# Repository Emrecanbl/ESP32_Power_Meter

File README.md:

# ESP32-S3 Power Meter (INA3221 ·  TFT · Qt Ui · SQLlite data base)

An ESP32-S3–based **three-channel power meter** built around INA3221. One channel supports **USB-C pass-through** so you can measure power flowing from **USB-C IN → USB-C OUT**; **CC pins are tied** for basic PD trigger behavior (power-only path).

> Firmware stack: **FreeRTOS**.
> REST/WebSocket API is **optional** (may be added later).
> Live data can be streamed over **USB-CDC**; an **optional ST7735 (160×128) SPI TFT** can show basic status (no touch).
>
> A custom **3D-printed enclosure** is planned.

---

---

## Features

* **3 measurement channels** via **INA3221**

  * Voltage (V), Current (A), Power (W), accumulated **mAh / mWh**
* **ESP32-S3** (Wi‑Fi + native USB/CDC)

  * UART header and USB device available on the board
* **USB‑C pass‑through (1 channel)**: measure power across IN → OUT

  * **CC lines tied** (basic PD role trigger; data lines not routed)
* **Optional TFT:** **ST7735 (160×128) SPI** for basic on-device status (no touch)
* **Battery**: **TP4056** Li‑ion charger + **AMS1117‑3.3** LDO
* **Enclosure**: custom **3D‑printed** case (to be published)

---

## What’s New

* Qt UI with Python and SQLite database integration

* Added boot-time Check screen: verifies Wi‑Fi link and sensor health before entering the UI.

* Check screen now shows connection status and the assigned IP address.

* Main screen updated to display the device IP for quick access to the Web UI.

* **ST7735 (160×128) screen added (no touch).**

* Energy counter buttons are active (Start/Stop/Reset)

* Sensor → UART JSON and Web UI hooked up

* 4-task FreeRTOS skeleton: sensor, screen, web, uart

## Gallery

<p align="center">
  &nbsp;&nbsp;
  <br>
  <em> First Check Screen &nbsp; | &nbsp; Main Screen </em>
</p>

<p align="center">
  &nbsp;&nbsp;
  <br>
  <em> First Run Without Screen &nbsp; | &nbsp; With ST7735</em>
</p>

<p align="center">
  &nbsp;&nbsp;
  <br>
  <em>3D board render &nbsp; | &nbsp; PCB layout</em>
</p>

<p align="center">
  <!-- Add your prototype photos below when ready -->
  &nbsp;&nbsp;
  <em>Prototype (front) </em>
</p>

<p align="center">
  <br>
  <em>Producted PCB (first article)</em>
</p>

<p align="center">
  <br>
  <em>Assembled PCB </em>
</p>

<p align="center">
  <br>
  <em>Schematic (block view)</em>
</p>

<p align="center">
  <br>
  <em> Qt Ui </em>
</p>

## Hardware Overview

* **MCU:** ESP32‑S3 module
* **Power Monitor:** INA3221 (three shunts)
* **Optional Display:** ST7735 (160×128) over SPI (no touch)
* **Power Path:** USB‑C IN, USB‑C OUT (pass‑through on Channel 1)
* **PMICs:** TP4056 Li‑ion charger, AMS1117‑3.3 regulator
* **Connectors:** 3× screw terminals (IN/OUT/GND), UART header, 2× USB‑C

### Block Diagram

```
USB-C IN ──┐                  ┌── USB-C OUT (pass-through)
           ├─ Shunt CH1  ─────┤
IN/OUT CH2 ├─ Shunt CH2  ─────┤──> Loads
IN/OUT CH3 ├─ Shunt CH3  ─────┘
           │
        INA3221  ── I2C ── ESP32-S3 ── SPI ── ST7735 TFT (optional)
                               ├─ (Optional) Wi‑Fi HTTP/WS
                               └─ USB‑CDC / UART (streaming)
```

---

## Default Pins

| Function                       | ESP32‑S3 Pin      |
| ------------------------------ | ----------------- |
| I2C SDA / SCL (INA3221)        | GPIO __ / __      |
| TFT (ST7735) MOSI / MISO / SCK | GPIO __ / __ / __ |
| TFT CS / DC / RST              | GPIO __ / __ / __ |
| UART RX / TX                   | GPIO __ / __      |
| USB‑CDC                        | Native (S3)       |

---

## Firmware (planned)

* **Framework:** FreeRTOS
* **Modules:**

  * `sensor` – INA3221 sampling, filtering, mAh/mWh accumulation
  * `ui` *(optional)* – minimal status pages on **ST7735**; device can run headless
  * *(Optional)* `web` – HTTP + WebSocket for live JSON
  * `usb_stream` – ASCII/JSON streaming over USB‑CDC (no file logging)
* **Example JSON (USB/Web, if enabled):**

```json
{"ch":1,"voltage":5.08,"current":1.12,"power":5.69,"mah_total":23.4,"mwh_total":118.9,"ts":1730529652}
```

---

### Efficiency Measurement

The board can measure real conversion efficiency by comparing input and output power:

* Channels: CH1 = input (P_in), CH2 = output (P_out)
* Instantaneous: η_inst = P_out / P_in
* Averaged (stable): EMA over 1–3 s → η_avg =  P̄_out / P̄_in
* Energy-based: η_energy = ΔmWh_out / ΔmWh_in (robust against short spikes)

## Repo Layout (suggested)

```
/hardware
  schematic.pdf
  gerber/
/firmware
  /main
    board.h
    app_sensor.c
    app_ui_tft.c
    app_usb_stream.c
    (optional) app_web.c
  sdkconfig.defaults
/Photos
  PCB.jpg
  PCB_Model.jpg
  Prototype.jpg
  Prototype_Back1.jpg
  Prototype_Back2.jpg
  Real_PCB.jpg
  Schematic.png
/enclosure
  stl/  (3D-printed case files)
```

---

## Roadmap

* [ ] Bring‑up: INA3221 I2C readout
* [ ] Publish 3D‑printed enclosure (STL)
* [ ] USB‑CDC live streaming (no on‑device logs)
* [ ] Minimal on-device status (ST7735)
* [ ] Calibration UI + NVS storage
* [ ] (Optional) REST/WS endpoints

---

## Notes & Safety

* USB‑C pass‑through is **power‑only** (data lines not connected).
* CC lines support **basic PD trigger behavior**; PD profile support is **limited**.
* Verify shunt resistor wattage and temperature rise.
* Provide adequate thermal copper for **TP4056** during charging.

---

## License

MIT (to be added).

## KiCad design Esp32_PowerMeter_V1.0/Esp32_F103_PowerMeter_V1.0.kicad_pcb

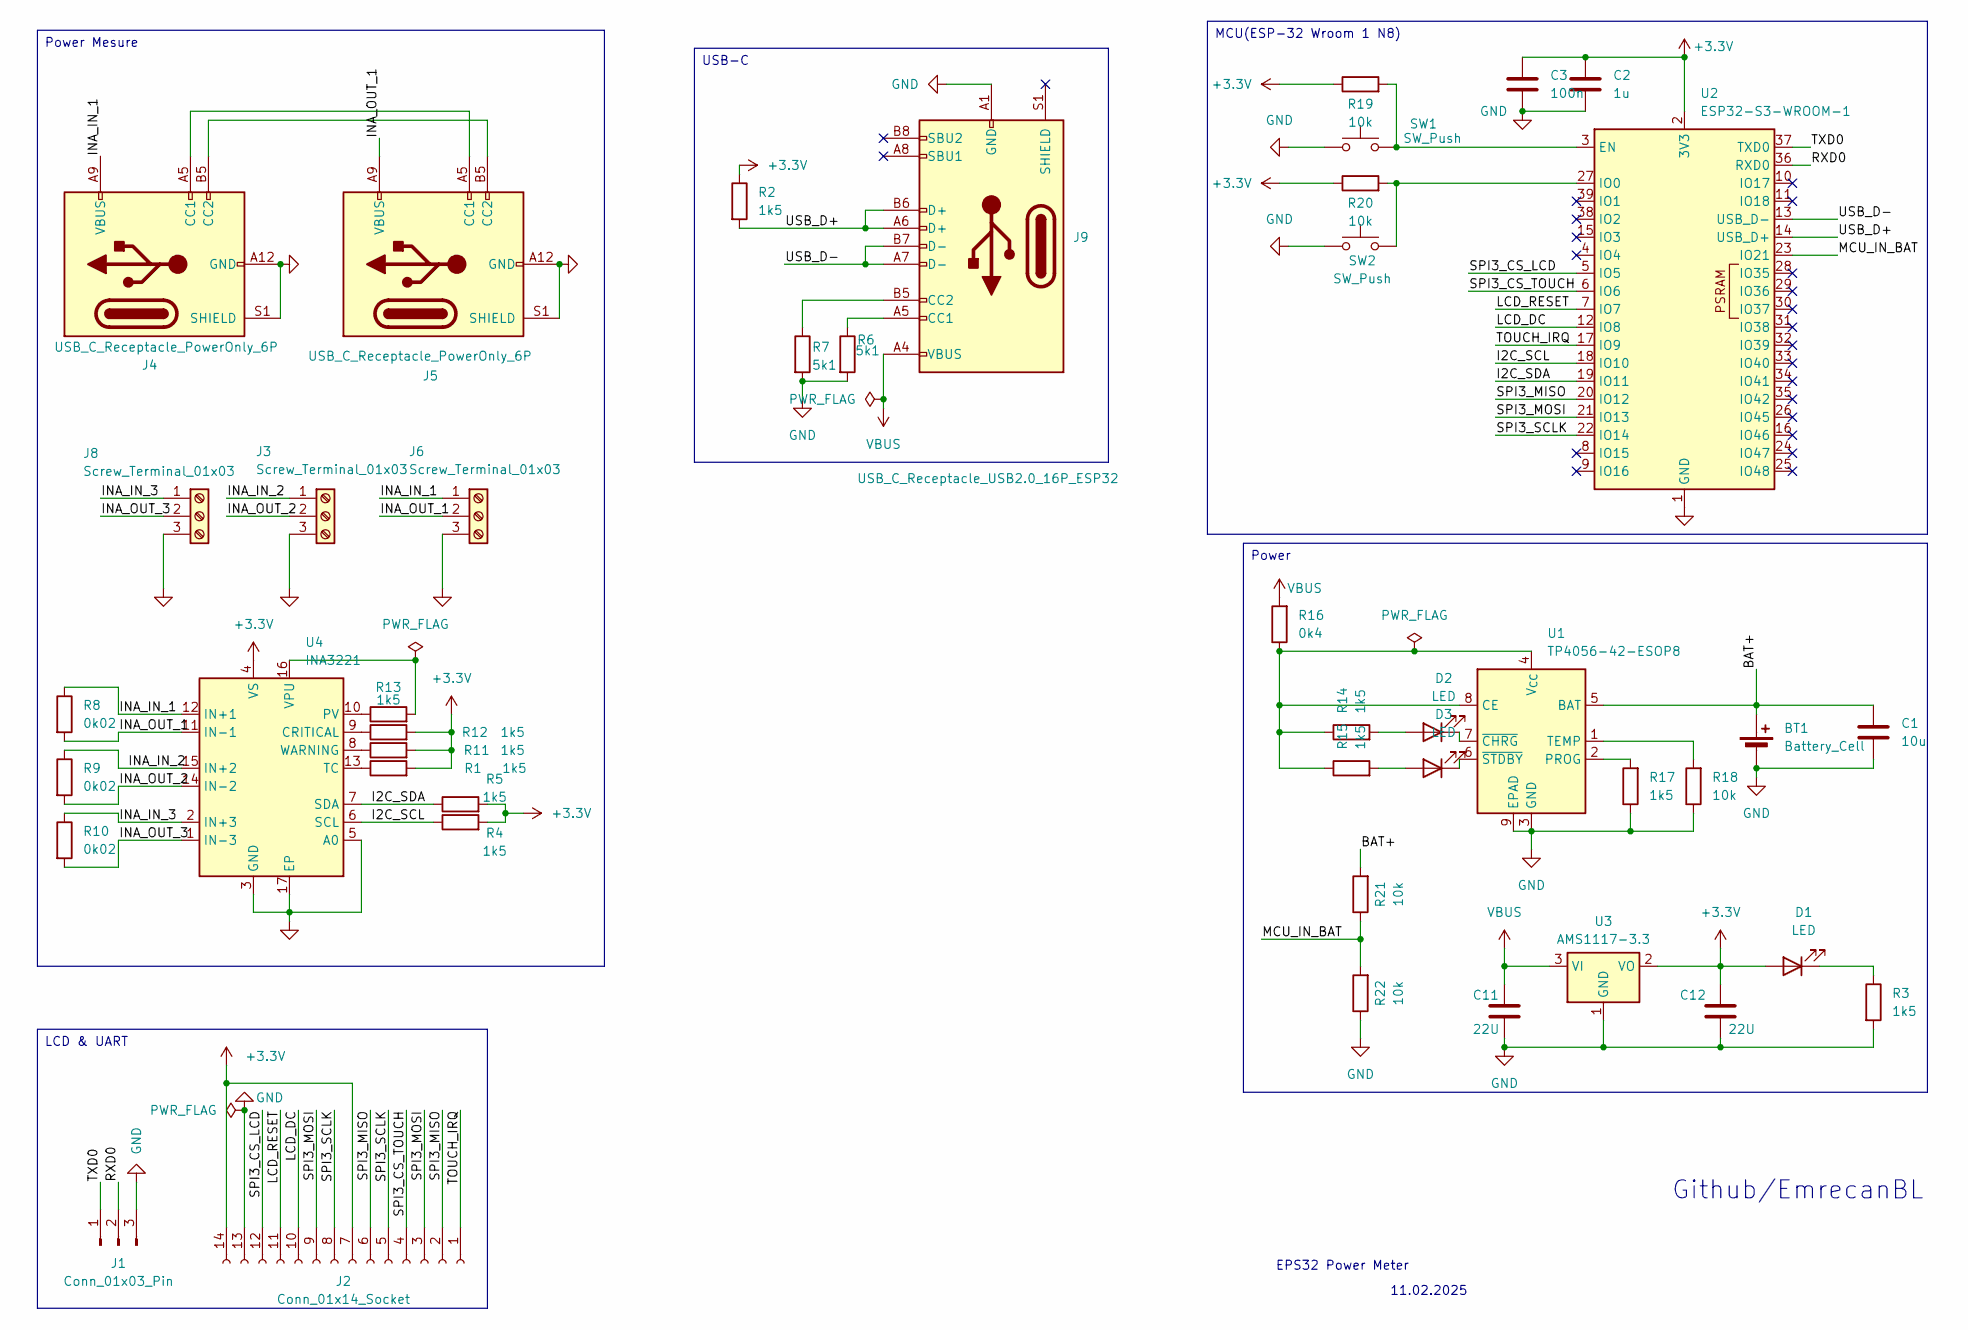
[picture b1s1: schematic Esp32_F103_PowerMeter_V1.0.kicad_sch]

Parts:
BT1: Battery_Cell; Molex_Micro-Fit_3.0_43045-0212_2x01_P3.00mm_Vertical
C1: 10u; C_0402_1005Metric
C2: 1u; C_0402_1005Metric
C3: 100n; C_0402_1005Metric
C11, C12: 22U; C_0603_1608Metric
D1, D2, D3: LED; LED_0603_1608Metric
J1: Conn_01x03_Pin; PinHeader_1x03_P2.54mm_Vertical
J2: Conn_01x14_Socket; PinSocket_1x14_P2.54mm_Vertical
J3, J6, J8: Screw_Terminal_01x03; TerminalBlock_4Ucon_1x03_P3.50mm_Vertical
J4, J5: USB_C_Receptacle_PowerOnly_6P; USB_C_Receptacle_GCT_USB4125-xx-x_6P_TopMnt_Horizontal
J9: USB_C_Receptacle_USB2.0_16P_ESP32; USB_C_Receptacle_GCT_USB4105-xx-A_16P_TopMnt_Horizontal
R1, R2, R3, R4, R5, R11, R12, R13, R14, R15, R17: 1k5; R_0603_1608Metric
R6, R7: 5k1; R_0603_1608Metric
R8, R9, R10: 0k02; R_0603_1608Metric
R16: 0k4; R_0603_1608Metric
R18, R19, R20, R21, R22: 10k; R_0603_1608Metric
SW1, SW2: SW_Push; SW_PUSH_6mm_H4.3mm
U1: TP4056-42-ESOP8; SOIC-8-1EP_3.9x4.9mm_P1.27mm_EP2.41x3.3mm_ThermalVias
U2: ESP32-S3-WROOM-1
U3: AMS1117-3.3; SOT-223-3_TabPin2
U4: INA3221; Texas_RGV0016A_VQFN-16-1EP_4x4mm_P0.65mm_EP2.1x2.1mm

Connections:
+3.3V: C2.1, C3.1, C12.1, D1.2 (A), J2.7, J2.14, R1.2, R2.1, R4.2, R5.2, R11.2, R12.2, R19.1, R20.1, U2.2 (3V3), U3.2 (VO), U4.4 (VS); also elsewhere on the board
/BAT+: BT1.1 (+), C1.1, R21.2, U1.5 (BAT)
/I2C_SCL: R4.1, U2.18 (IO10), U4.6 (SCL)
/I2C_SDA: R5.1, U2.19 (IO11), U4.7 (SDA)
/INA_IN_1: J4.A9 (VBUS), J4.B9 (VBUS), J6.1, R8.1, U4.12 (IN+1)
/INA_IN_2: J3.1, R9.1, U4.15 (IN+2)
/INA_IN_3: J8.1, R10.1, U4.2 (IN+3)
/INA_OUT_1: J5.A9 (VBUS), J5.B9 (VBUS), J6.2, R8.2, U4.11 (IN-1)
/INA_OUT_2: J3.2, R9.2, U4.14 (IN-2)
/INA_OUT_3: J8.2, R10.2, U4.1 (IN-3)
/LCD_DC: J2.10, U2.12 (IO8)
/LCD_RESET: J2.11, U2.7 (IO7)
/MCU_IN_BAT: R21.1, R22.2, U2.23 (IO21)
/RXD0: J1.2, U2.36 (RXD0)
/SPI3_CS_LCD: J2.12, U2.5 (IO5)
/SPI3_CS_TOUCH: J2.4, U2.6 (IO6)
/SPI3_MISO: J2.2, J2.6, U2.20 (IO12)
/SPI3_MOSI: J2.3, J2.9, U2.21 (IO13)
/SPI3_SCLK: J2.5, J2.8, U2.22 (IO14)
/TOUCH_IRQ: J2.1, U2.17 (IO9)
/TXD0: J1.1, U2.37 (TXD0)
/USB_D+: J9.A6 (D+), J9.B6 (D+), R2.2, U2.14 (USB_D+)
/USB_D-: J9.A7 (D-), J9.B7 (D-), U2.13 (USB_D-)
GND: BT1.2 (-), C1.2, C2.2, C3.2, C11.2, C12.2, J1.3, J2.13, J3.3, J4.A12 (GND), J4.B12 (GND), J4.S1 (SHIELD), J5.A12 (GND), J5.B12 (GND), J5.S1 (SHIELD), J6.3, J8.3, J9.A1 (GND), J9.A12 (GND), J9.B1 (GND), J9.B12 (GND), R3.2, R6.2, R7.2, R17.1, R18.1, R22.1, SW1.1, SW2.1, U1.3 (GND), U1.9 (EPAD), U2.1 (GND), U2.40 (GND), U2.41 (GND), U3.1 (GND), U4.3 (GND), U4.5 (A0), U4.17 (EP); also elsewhere on the board
unnamed: D1.1 (K), R3.1
unnamed: D2.2 (A), R14.2
unnamed: D2.1 (K), U1.7 (~CHRG)
unnamed: D3.2 (A), R15.2
unnamed: D3.1 (K), U1.6 (~STDBY)
unnamed: J4.A5 (CC1), J5.A5 (CC1)
unnamed: J4.B5 (CC2), J5.B5 (CC2)
unnamed: J9.A5 (CC1), R6.1
unnamed: J9.B5 (CC2), R7.1
unnamed: R14.1, R15.1, R16.1, U1.4 (V_{CC}), U1.8 (CE)
unnamed: R17.2, U1.2 (PROG)
unnamed: R18.2, U1.1 (TEMP)
unnamed: R19.2, SW1.2, U2.3 (EN)
unnamed: R20.2, SW2.2, U2.27 (IO0)
unnamed: R12.1, U4.9 (CRITICAL)
unnamed: R13.1, U4.10 (PV)
unnamed: R1.1, U4.13 (TC)
unnamed: R13.2, U4.16 (VPU)
unnamed: R11.1, U4.8 (WARNING)
VBUS: C11.1, J9.A4 (VBUS), J9.A9 (VBUS), J9.B4 (VBUS), J9.B9 (VBUS), R16.2, U3.3 (VI)

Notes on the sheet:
11.02.2025
Github/EmrecanBL
EPS32 Power Meter
USB-C
LCD & UART
Power
MCU(ESP-32 Wroom 1 N8)
Power Mesure

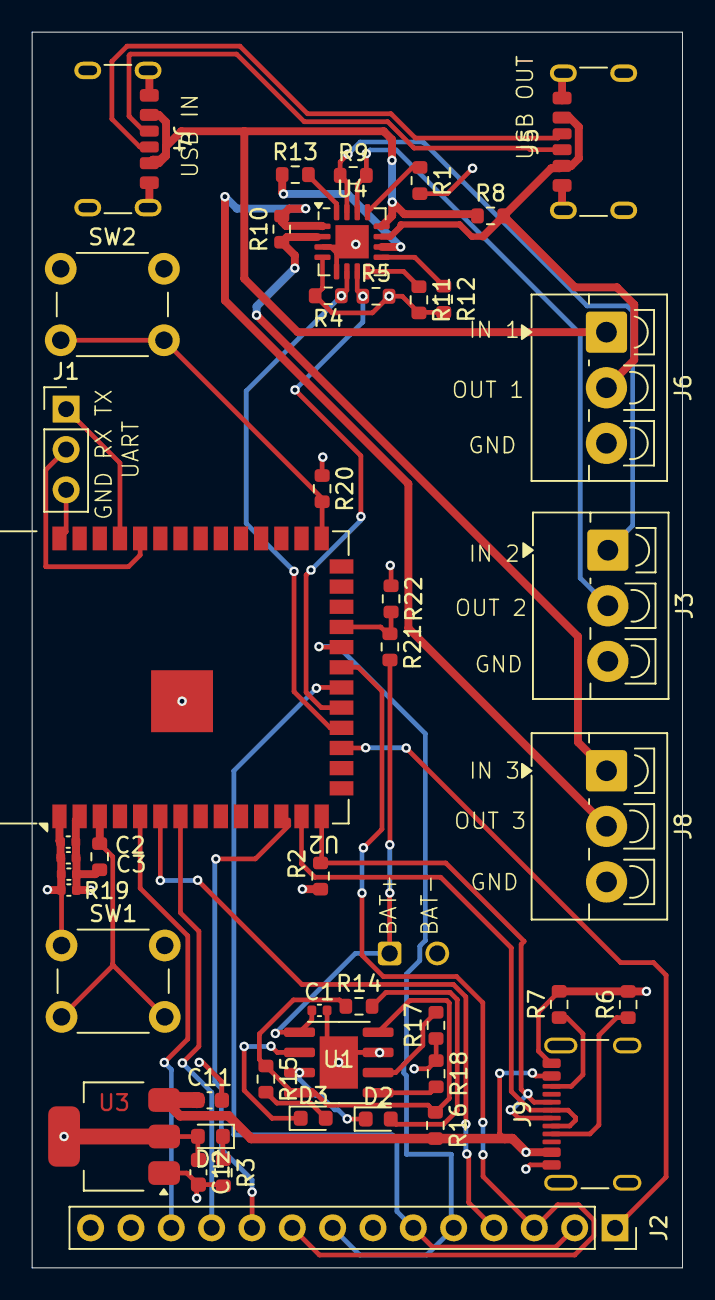
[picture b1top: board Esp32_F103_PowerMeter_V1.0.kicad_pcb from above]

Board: 4 copper layers, 41.0 x 77.8 mm, 47 parts (0 on the bottom side), 44 nets.

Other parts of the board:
C2#2: 1u; C_0402_1005Metric
C3#2: 100n; C_0402_1005Metric

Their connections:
+3.3V: C2#2.1, C3#2.1; also elsewhere on the board
GND: C2#2.2, C3#2.2; also elsewhere on the board

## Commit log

2025-11-02 Project Created
2025-11-02 Readme_Update
2025-11-03 PCB_Assambled
    PCB foto update
2025-11-03 PCB_Assembled
    PCB Assembled Photo
2025-11-03 WEBUI_Photo
2025-11-04 Firmware first version
    Sensor, WEB Ui and Uart Integrated
2025-11-05 Function Update
2025-11-05 Value_Reset
2025-11-05 Screen_St7735_Update
2025-11-05 Wifi and Sensor check
2025-11-06 Screen_Update
2025-11-10 Qt Ui
2025-11-17 Buton_update
